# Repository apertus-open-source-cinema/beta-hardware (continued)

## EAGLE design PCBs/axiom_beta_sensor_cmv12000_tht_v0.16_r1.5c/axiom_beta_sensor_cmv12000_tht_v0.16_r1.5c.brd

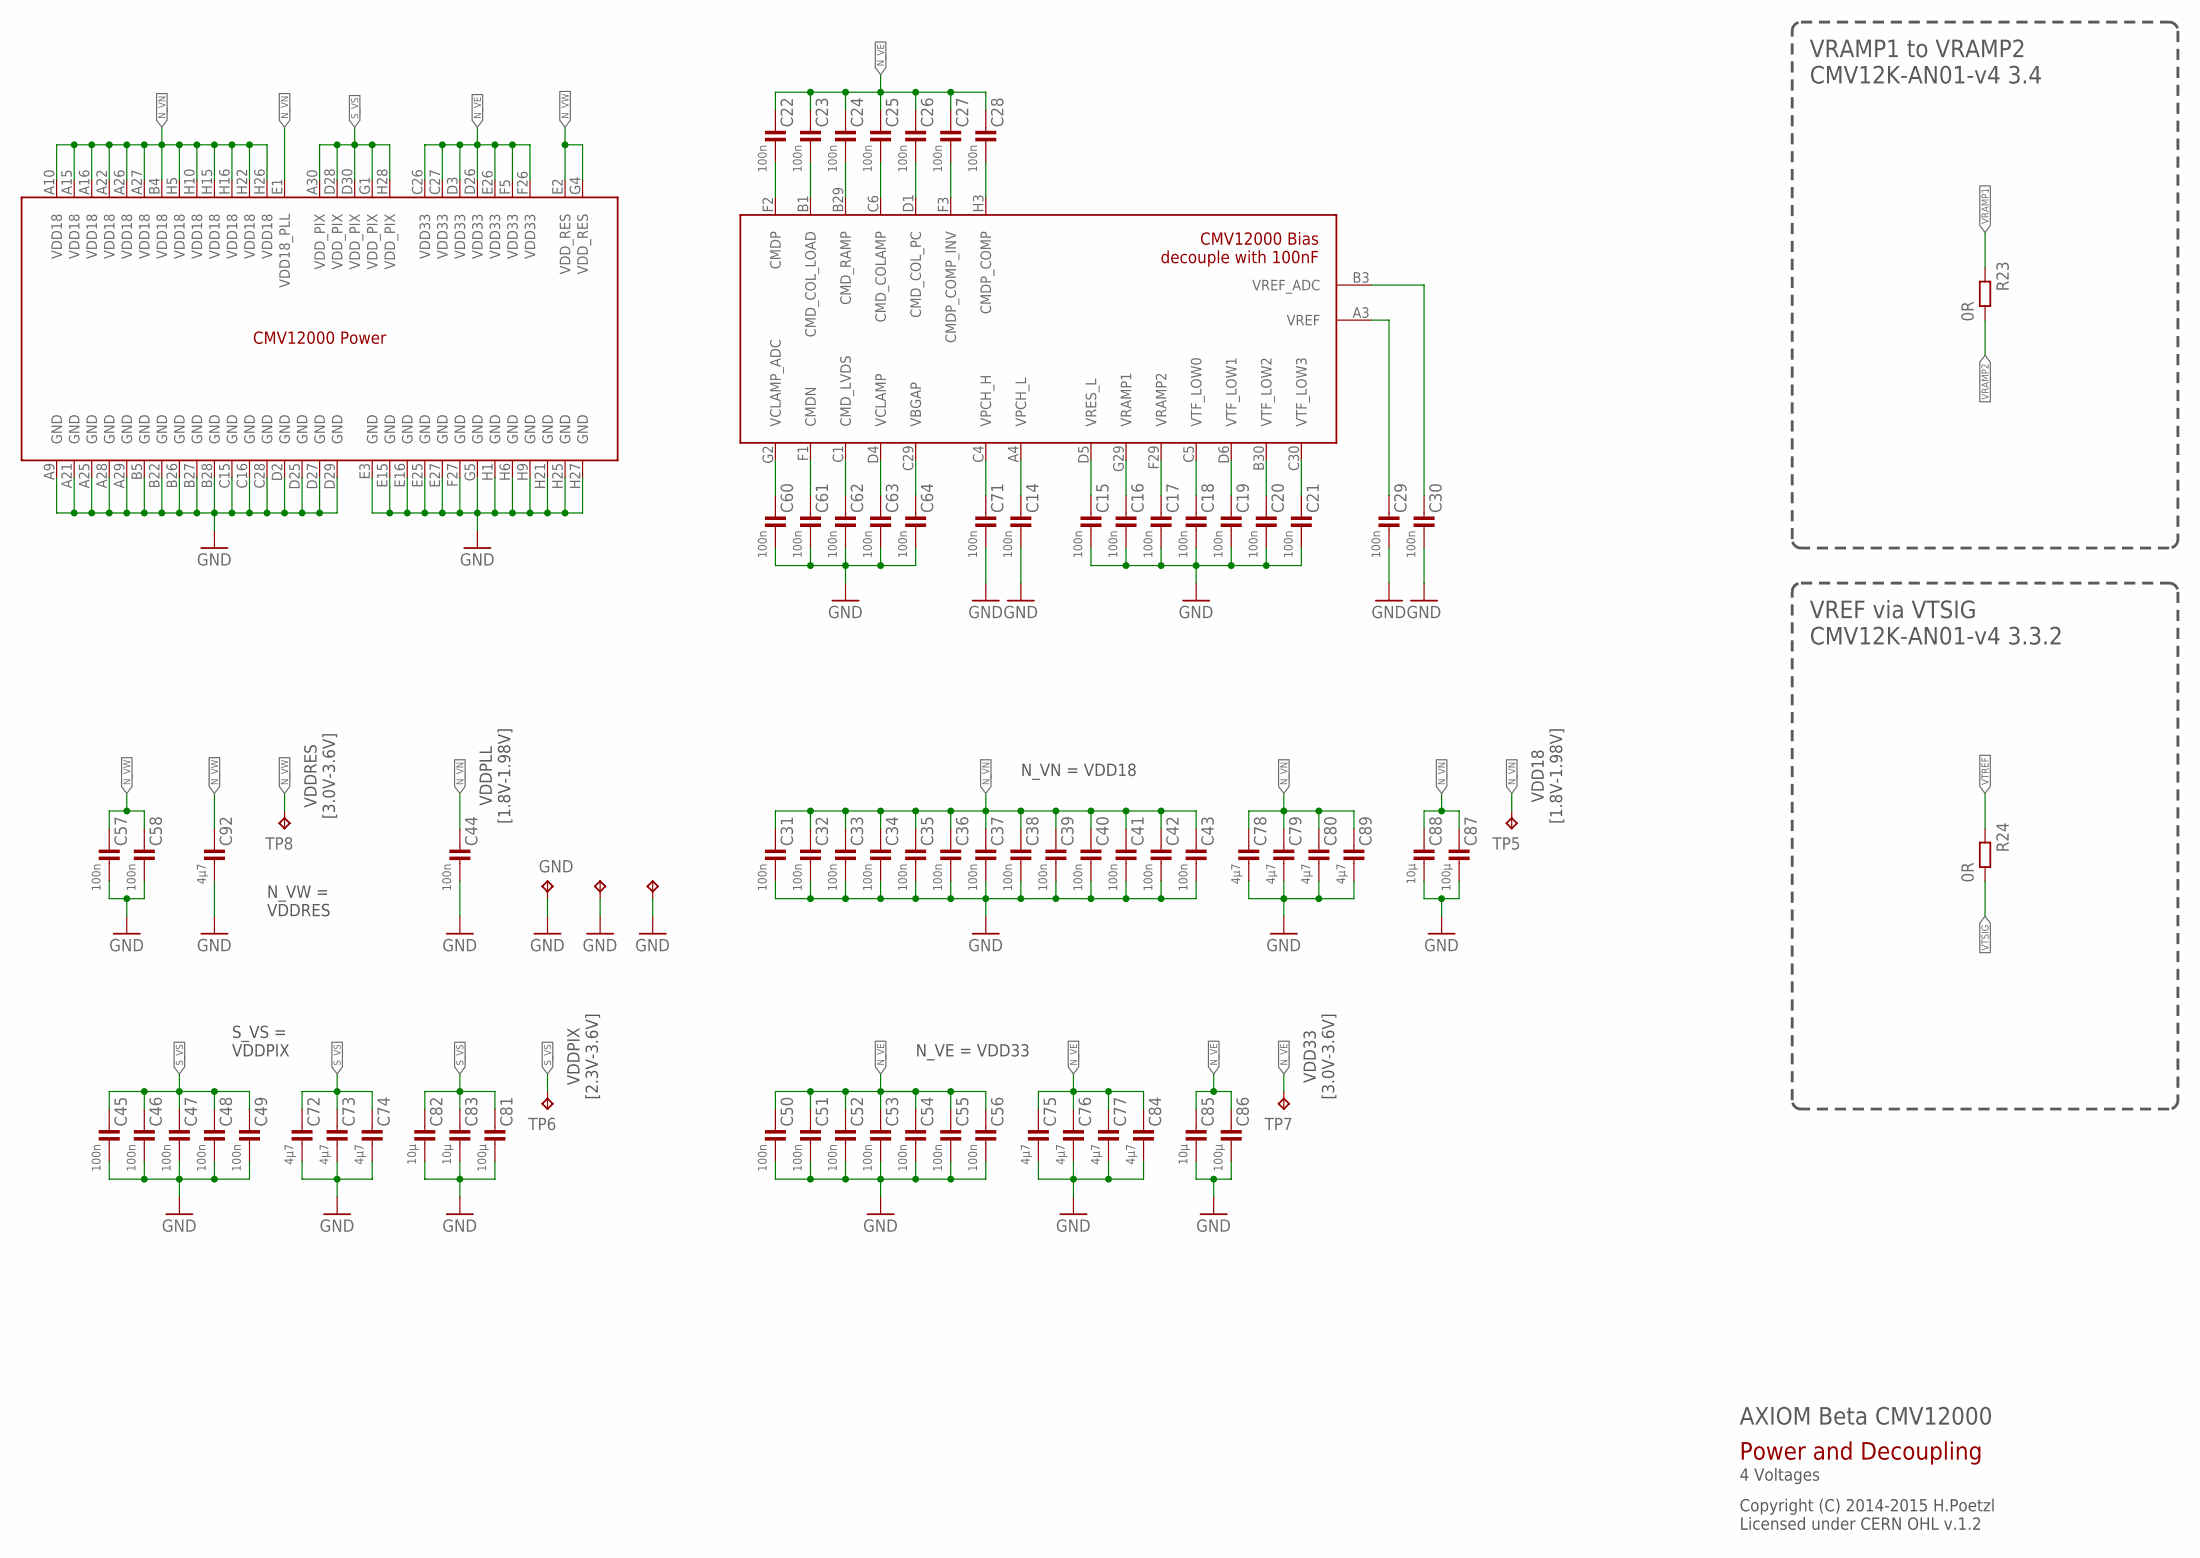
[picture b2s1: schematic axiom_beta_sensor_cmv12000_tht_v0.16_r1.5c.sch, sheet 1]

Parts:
C14, C15, C16, C17, C18, C19, C20, C21, C22, C23, C24, C25, C26, C27, C28, C29, C30, C31, C32, C33, C34, C35, C36, C37, C38, C39, C40, C41, C42, C43, C44, C45, C46, C47, C48, C49, C50, C51, C52, C53, C54, C55, C56, C57, C58, C60, C61, C62, C63, C64, C71: 100n; 0402-C
C72, C77, C78: 4µ7; 0402-B
C73, C74, C75, C76, C79, C80, C84, C89, C92: 4µ7; 0402-C
C81, C86, C87: 100µ; 1206-B
C82, C83, C85, C88: 10µ; 0603-C
GND, GND75, GND77: TPTP10R; TP10R
R23, R24: 0R; 0402-C
SENSOR: CMV12000ANDON; 10-30-07-237-400T4
TP5, TP6, TP7, TP8: TPTP10R; TP10R

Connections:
GND: C14.2, C15.2, C16.2, C17.2, C18.2, C19.2, C20.2, C21.2, C29.2, C30.2, C31.2, C32.2, C33.2, C34.2, C35.2, C36.2, C37.2, C38.2, C39.2, C40.2, C41.2, C42.2, C43.2, C44.2, C45.2, C46.2, C47.2, C48.2, C49.2, C50.2, C51.2, C52.2, C53.2, C54.2, C55.2, C56.2, C57.2, C58.2, C60.2, C61.2, C62.2, C63.2, C64.2, C71.2, C72.2, C73.2, C74.2, C75.2, C76.2, C77.2, C78.2, C79.2, C80.2, C81.2, C82.2, C83.2, C84.2, C85.2, C86.2, C87.2, C88.2, C89.2, C92.2, GND.TP, GND75.TP, GND77.TP, SENSOR.A9 (GND), SENSOR.A21 (GND), SENSOR.A25 (GND), SENSOR.A28 (GND), SENSOR.A29 (GND), SENSOR.B5 (GND), SENSOR.B22 (GND), SENSOR.B26 (GND), SENSOR.B27 (GND), SENSOR.B28 (GND), SENSOR.C15 (GND), SENSOR.C16 (GND), SENSOR.C28 (GND), SENSOR.D2 (GND), SENSOR.D25 (GND), SENSOR.D27 (GND), SENSOR.D29 (GND), SENSOR.E3 (GND), SENSOR.E15 (GND), SENSOR.E16 (GND), SENSOR.E25 (GND), SENSOR.E27 (GND), SENSOR.F27 (GND), SENSOR.G5 (GND), SENSOR.H1 (GND), SENSOR.H6 (GND), SENSOR.H9 (GND), SENSOR.H21 (GND), SENSOR.H25 (GND), SENSOR.H27 (GND); also elsewhere on the board
unnamed: C60.1, SENSOR.G2 (VCLAMP_ADC)
unnamed: C61.1, SENSOR.F1 (CMDN)
unnamed: C62.1, SENSOR.C1 (CMD_LVDS)
unnamed: C63.1, SENSOR.D4 (VCLAMP)
unnamed: C64.1, SENSOR.C29 (VBGAP)
unnamed: C71.1, SENSOR.C4 (VPCH_H)
unnamed: C14.1, SENSOR.A4 (VPCH_L)
unnamed: C15.1, SENSOR.D5 (VRES_L)
unnamed: C18.1, SENSOR.C5 (VTF_LOW0)
unnamed: C19.1, SENSOR.D6 (VTF_LOW1)
unnamed: C20.1, SENSOR.B30 (VTF_LOW2)
unnamed: C21.1, SENSOR.C30 (VTF_LOW3)
unnamed: C22.2, SENSOR.F2 (CMDP)
unnamed: C23.2, SENSOR.B1 (CMD_COL_LOAD)
unnamed: C24.2, SENSOR.B29 (CMD_RAMP)
unnamed: C25.2, SENSOR.C6 (CMD_COLAMP)
unnamed: C26.2, SENSOR.D1 (CMD_COL_PC)
unnamed: C27.2, SENSOR.F3 (CMDP_COMP_INV)
unnamed: C28.2, SENSOR.H3 (CMDP_COMP)
unnamed: C29.1, SENSOR.A3 (VREF)
unnamed: C30.1, SENSOR.B3 (VREF_ADC)
N_VE: C22.1, C23.1, C24.1, C25.1, C26.1, C27.1, C28.1, C50.1, C51.1, C52.1, C53.1, C54.1, C55.1, C56.1, C75.1, C76.1, C77.1, C84.1, C85.1, C86.1, SENSOR.C26 (VDD33), SENSOR.C27 (VDD33), SENSOR.D3 (VDD33), SENSOR.D26 (VDD33), SENSOR.E26 (VDD33), SENSOR.F5 (VDD33), SENSOR.F26 (VDD33), TP7.TP; also elsewhere on the board
N_VN: C31.1, C32.1, C33.1, C34.1, C35.1, C36.1, C37.1, C38.1, C39.1, C40.1, C41.1, C42.1, C43.1, C44.1, C78.1, C79.1, C80.1, C87.1, C88.1, C89.1, SENSOR.A10 (VDD18), SENSOR.A15 (VDD18), SENSOR.A16 (VDD18), SENSOR.A22 (VDD18), SENSOR.A26 (VDD18), SENSOR.A27 (VDD18), SENSOR.B4 (VDD18), SENSOR.E1 (VDD18_PLL), SENSOR.H5 (VDD18), SENSOR.H10 (VDD18), SENSOR.H15 (VDD18), SENSOR.H16 (VDD18), SENSOR.H22 (VDD18), SENSOR.H26 (VDD18), TP5.TP; also elsewhere on the board
N_VW: C57.1, C58.1, C92.1, SENSOR.E2 (VDD_RES), SENSOR.G4 (VDD_RES), TP8.TP; also elsewhere on the board
S_VS: C45.1, C46.1, C47.1, C48.1, C49.1, C72.1, C73.1, C74.1, C81.1, C82.1, C83.1, SENSOR.A30 (VDD_PIX), SENSOR.D28 (VDD_PIX), SENSOR.D30 (VDD_PIX), SENSOR.G1 (VDD_PIX), SENSOR.H28 (VDD_PIX), TP6.TP; also elsewhere on the board
VRAMP1: C16.1, R23.1, SENSOR.G29 (VRAMP1)
VRAMP2: C17.1, R23.2, SENSOR.F29 (VRAMP2)
VTREF: R24.1; also elsewhere on the board
VTSIG: R24.2; also elsewhere on the board

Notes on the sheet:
N_VN = VDD18
N_VE = VDD33
VDDPIX [2.3V-3.6V]
VDDRES [3.0V-3.6V]
VREF via VTSIG CMV12K-AN01-v4 3.3.2
VRAMP1 to VRAMP2 CMV12K-AN01-v4 3.4
AXIOM Beta CMV12000
Copyright (C) 2014-2015 H.Poetzl Licensed under CERN OHL v.1.2
Power and Decoupling
4 Voltages
VDD18 [1.8V-1.98V]
VDD33 [3.0V-3.6V]
VDDPLL [1.8V-1.98V]
S_VS = VDDPIX
N_VW = VDDRES
